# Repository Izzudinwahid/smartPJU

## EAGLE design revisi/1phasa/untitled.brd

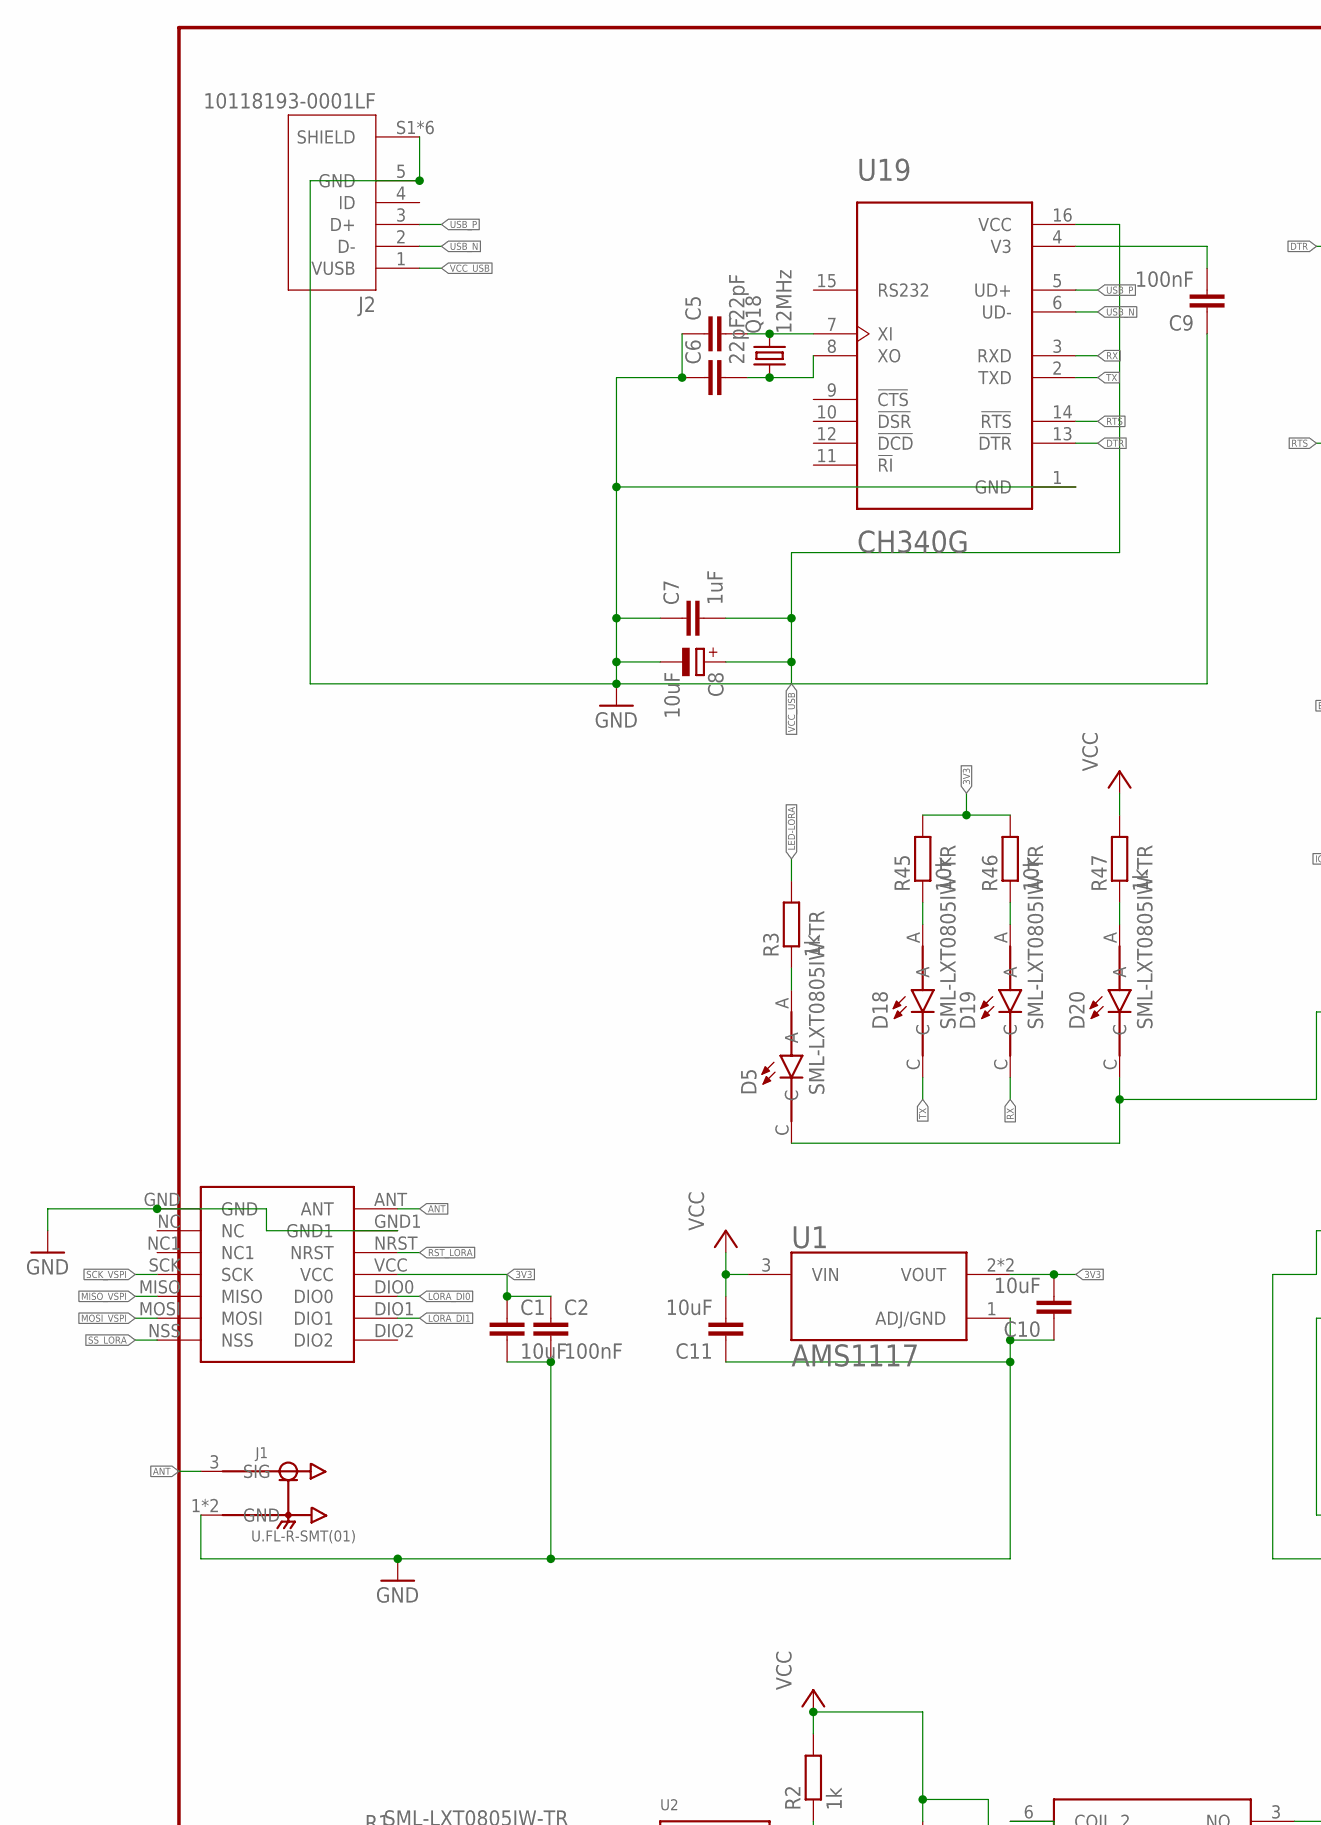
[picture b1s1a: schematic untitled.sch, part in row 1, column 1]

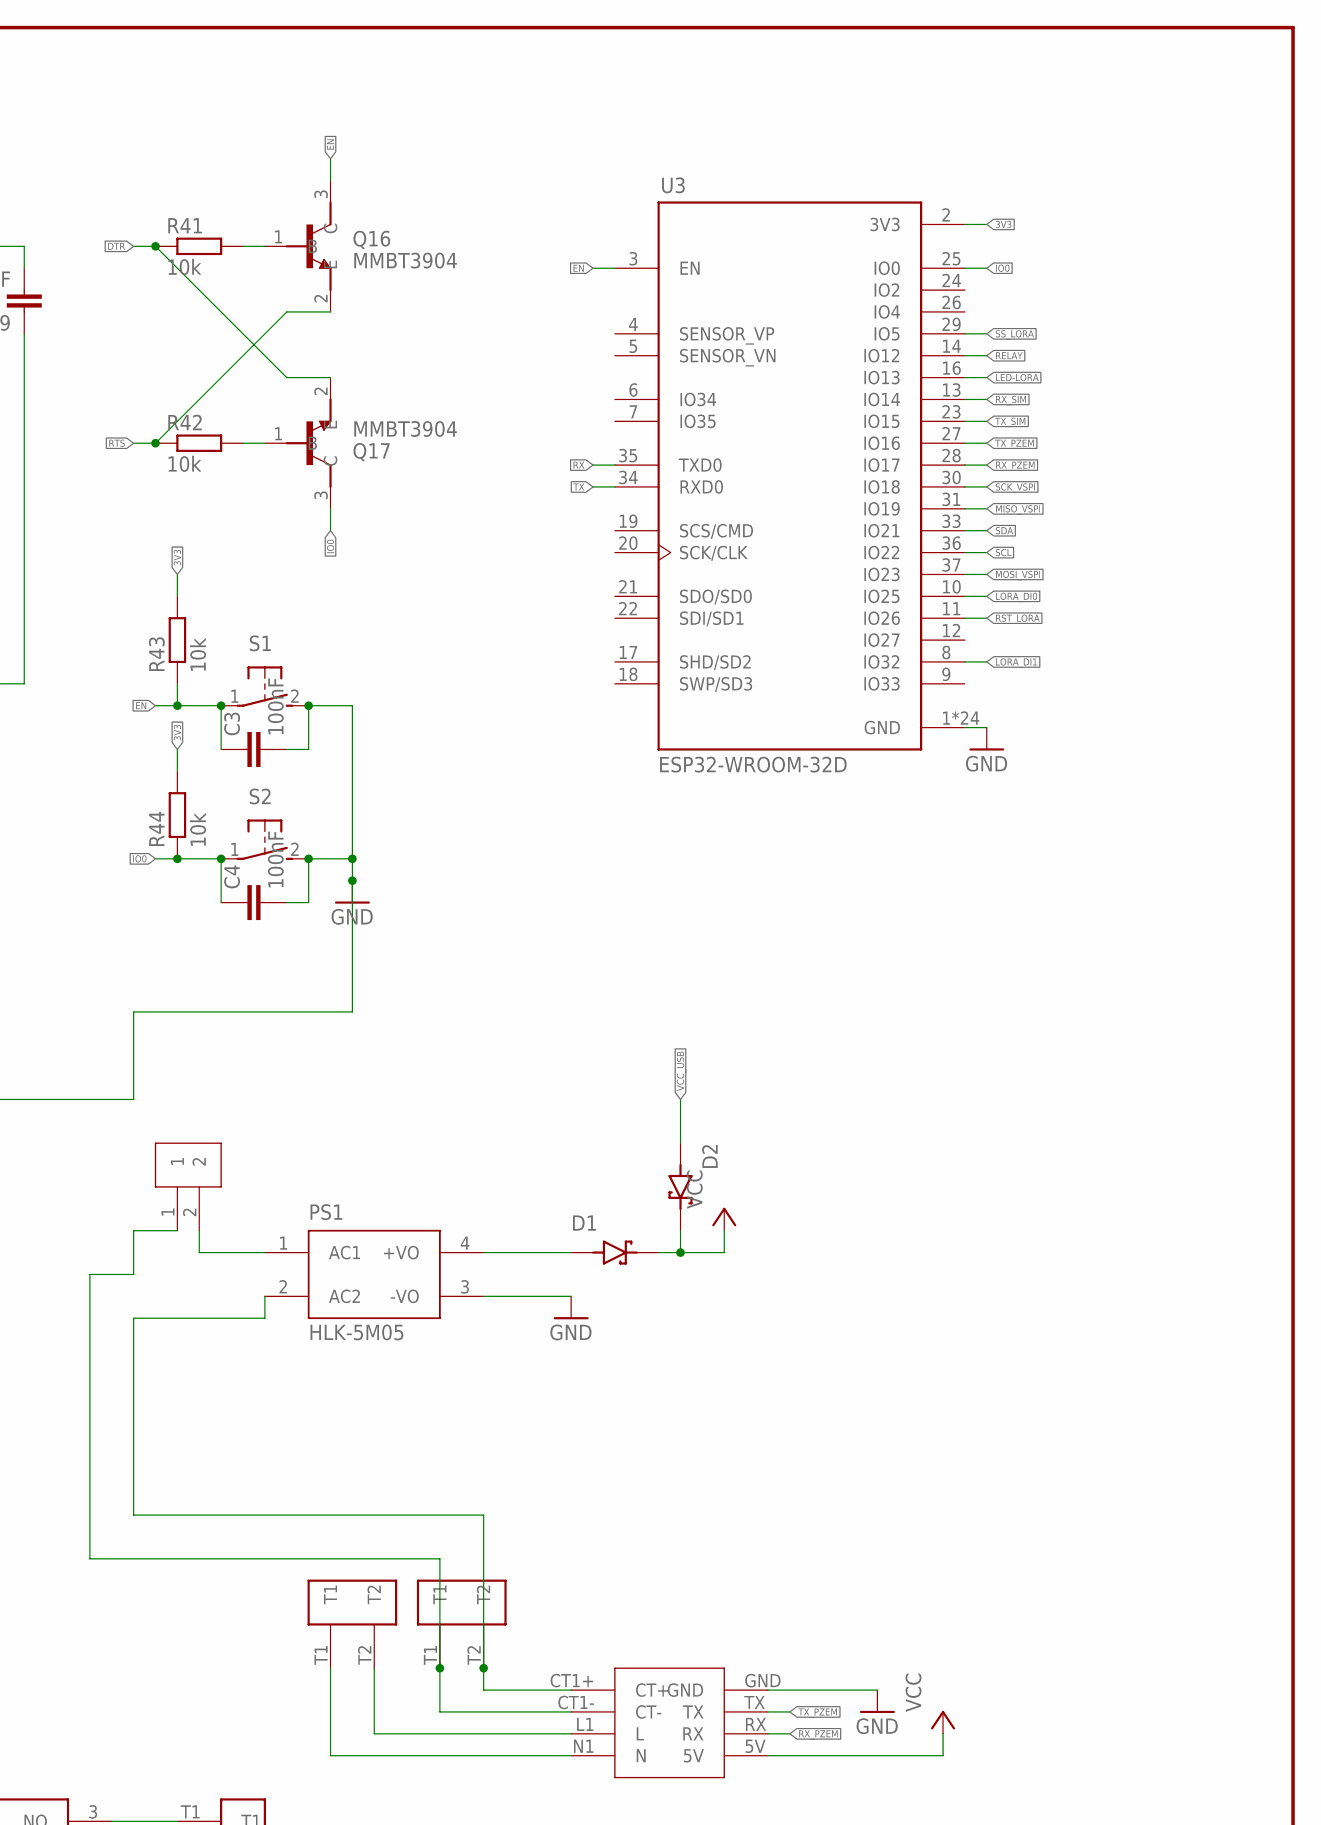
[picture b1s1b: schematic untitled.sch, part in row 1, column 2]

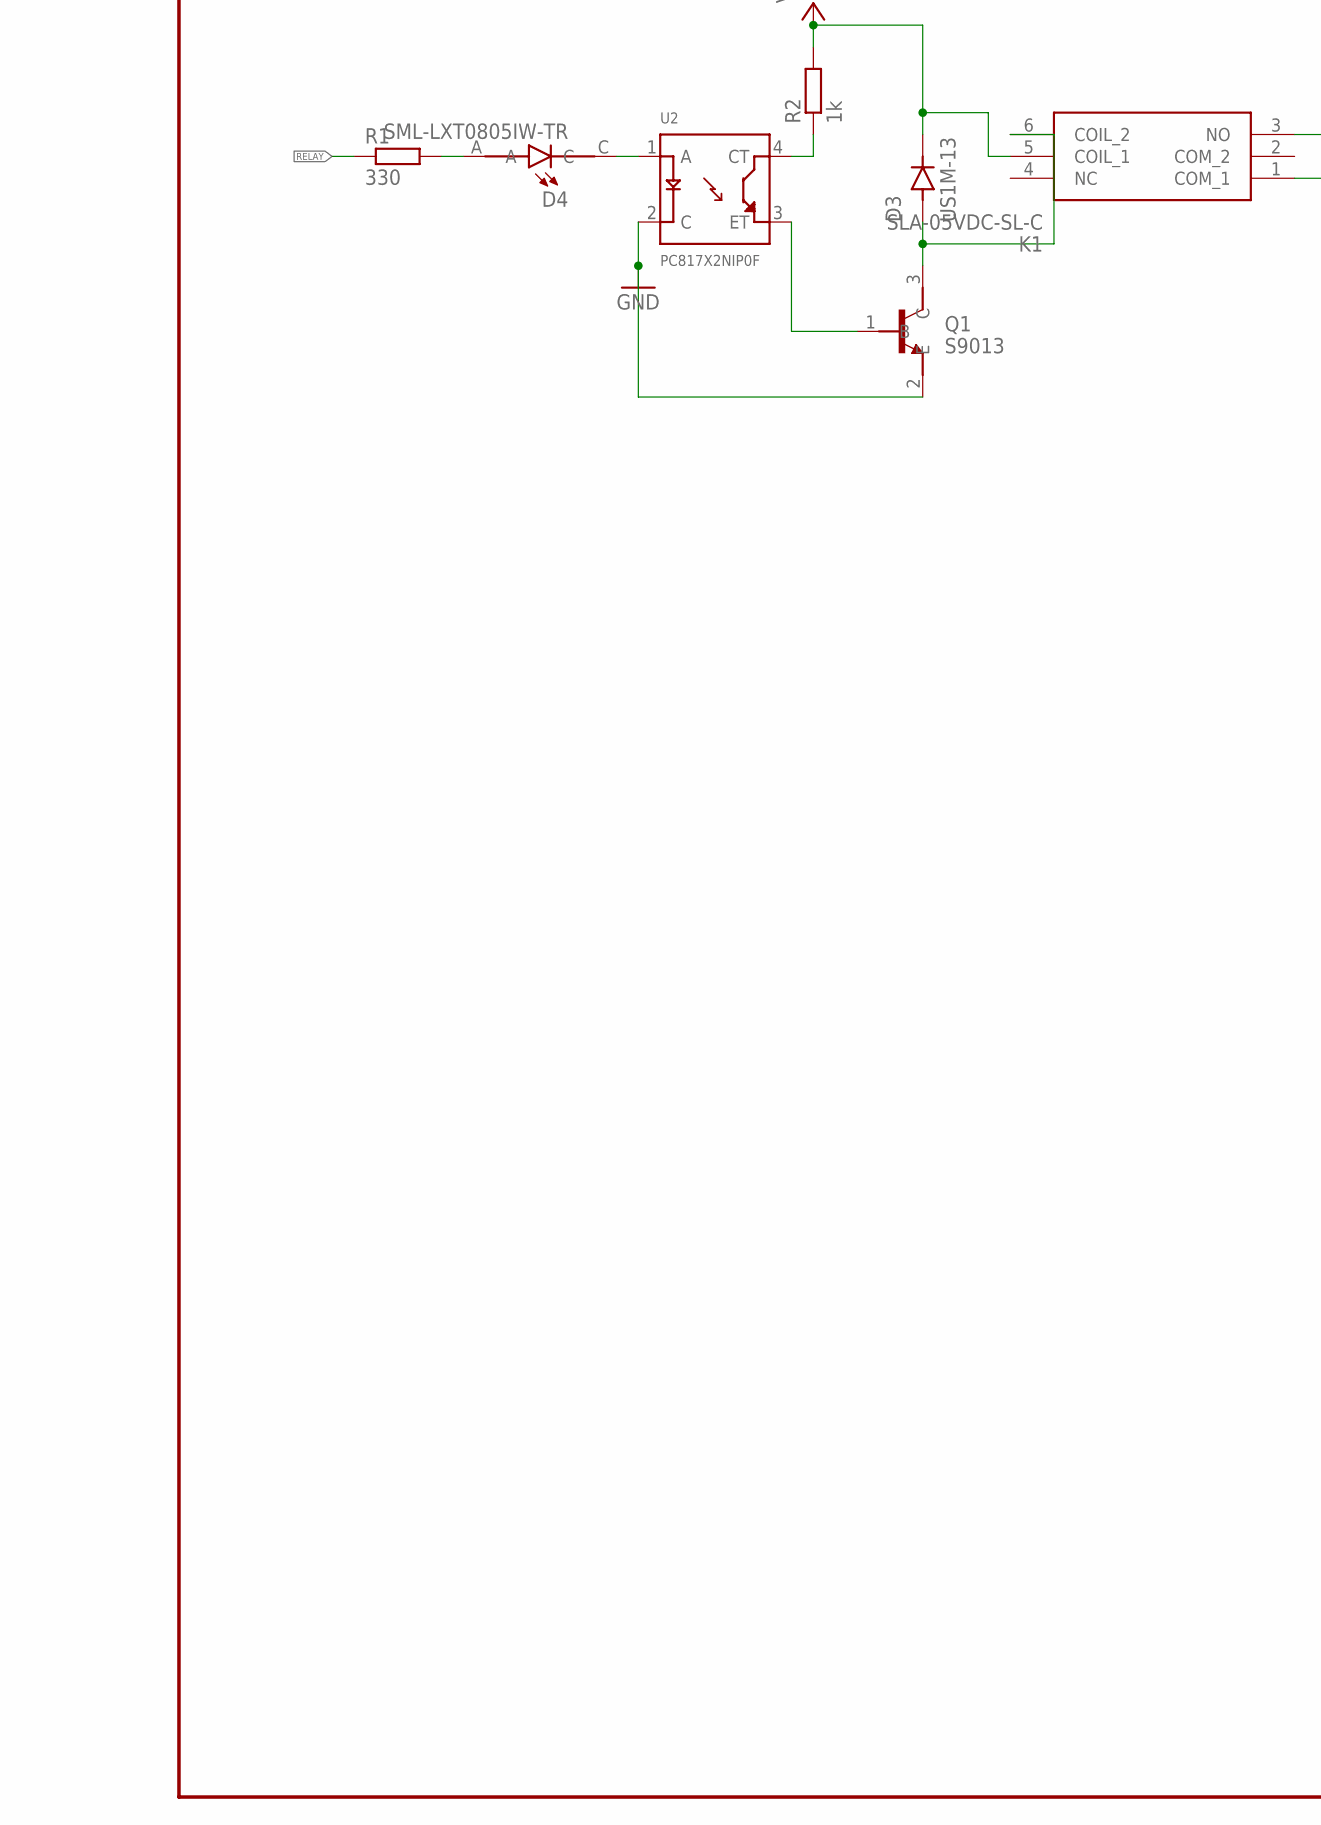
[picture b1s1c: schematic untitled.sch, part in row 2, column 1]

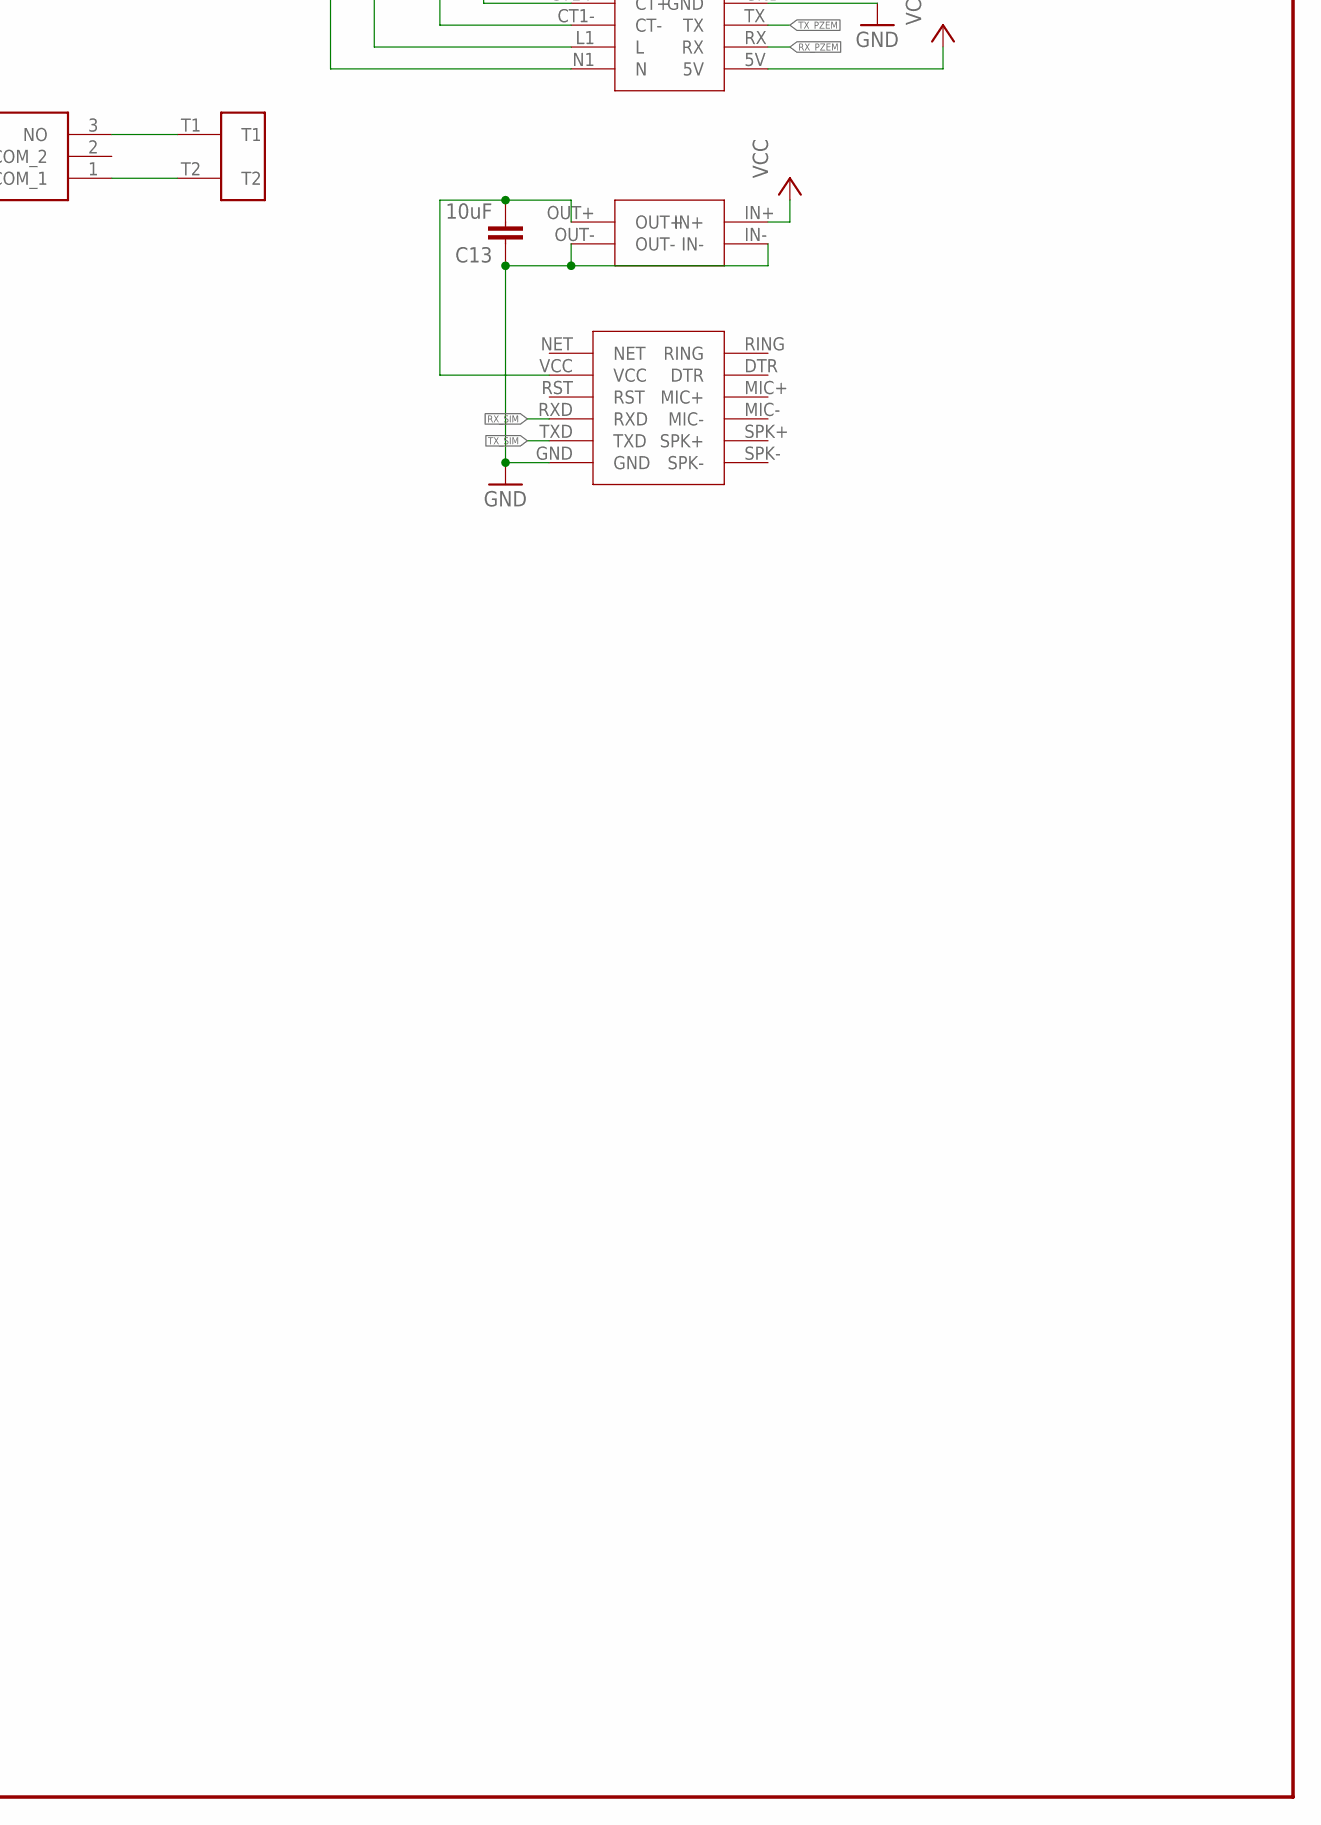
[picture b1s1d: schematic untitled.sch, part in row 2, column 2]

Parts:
C1, C10, C11, C13: 10uF; C0805K
C2, C3, C4, C9: 100nF; C0805K
C5, C6: 22pF; C0805K
C7: 1uF; C0805K
C8: 10uF; 153CLV-0505
D1, D2: 1N5819HW-7; SOD3715X145N
D3: US1M-13; DIOM5226X240N
D4, D5, D18, D19, D20: SML-LXT0805IW-TR; LEDC2012X120N
FUSE-KOTAK1: FUSE-KOTAK
J1: U.FL-R-SMT(01); HRS_U.FL-R-SMT(01)
J2: 10118193-0001LF; FCI_10118193-0001LF
K1: SLA-05VDC-SL-C; SLA05VDCSLC
LORA-NICERF-V1: LORA-NICERF-V2
MINI1: MINI360
PS1: HLK-5M05; CONV_HLK-5M05
PZEM004T1: PZEM004T
Q1: S9013; SOT95P240X120-3N
Q16, Q17: MMBT3904; SOT95P240X120-3N
Q18: 12MHz; SM49
R1: 330; R0805
R2, R3, R47: 1k; R0805
R41, R42, R43, R44, R45, R46: 10k; R0805
S1, S2: 31-XX; B3F-31XX
SIM800L1: SIM800L
TB7.2, TB7.3, TB7.4: TB7.62
U1: AMS1117; SOT229P700X180-4N
U2: PC817X2NIP0F; SOT254P975X400-4N
U3: ESP32-WROOM-32D; MODULE_ESP32-WROOM-32D
U19: CH340G; SOIC127P600X180-16N

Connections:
3V3: C1.1, C2.1, C10.2, LORA-NICERF-V1.VCC, R43.2, R44.2, R45.2, R46.2, U1.2 (VOUT), U1.4 (VOUT), U3.2 (3V3)
ANT: J1.3 (SIG), LORA-NICERF-V1.ANT
DTR: Q17.2 (E), R41.1, U19.13 (!DTR)
EN: C3.1, Q16.3 (C), R43.1, S1.1, U3.3 (EN)
GND: C1.2, C2.2, C3.2, C4.2, C5.1, C6.1, C7.1, C8.-, C9.1, C10.1, C11.1, C13.1, D5.C, D20.C, J1.1 (GND), J1.2 (GND), J2.5 (GND), J2.S1 (SHIELD), J2.S2 (SHIELD), J2.S3 (SHIELD), J2.S4 (SHIELD), J2.S5 (SHIELD), J2.S6 (SHIELD), LORA-NICERF-V1.GND, LORA-NICERF-V1.GND1, MINI1.IN-, MINI1.OUT-, PS1.3 (-VO), PZEM004T1.GND, Q1.2 (E), S1.2 (S), S2.2 (S), SIM800L1.GND, U1.1 (ADJ/GND), U2.2 (C), U3.1 (GND), U3.15 (GND), U3.38 (GND), U3.39_1 (GND), U3.39_2 (GND), U3.39_3 (GND), U3.39_4 (GND), U3.39_5 (GND), U3.39_6 (GND), U3.39_7 (GND), U3.39_8 (GND), U3.39_9 (GND), U3.39_10 (GND), U3.39_11 (GND), U3.39_12 (GND), U3.39_13 (GND), U3.39_14 (GND), U3.39_15 (GND), U3.39_16 (GND), U3.39_17 (GND), U3.39_18 (GND), U3.39_19 (GND), U3.39_20 (GND), U3.39_21 (GND), U19.1 (GND)
IO0: C4.1, Q17.3 (C), R44.1, S2.1, U3.25 (IO0)
LED-LORA: R3.2, U3.16 (IO13)
LORA_DI0: LORA-NICERF-V1.DIO0, U3.10 (IO25)
LORA_DI1: LORA-NICERF-V1.DIO1, U3.8 (IO32)
MISO_VSPI: LORA-NICERF-V1.MISO, U3.31 (IO19)
MOSI_VSPI: LORA-NICERF-V1.MOSI, U3.37 (IO23)
unnamed: FUSE-KOTAK1.2, PS1.1 (AC1)
unnamed: PS1.2 (AC2), PZEM004T1.CT1+ (CT+), TB7.3.T2
unnamed: D1.A, PS1.4 (+VO)
unnamed: D4.C, U2.1 (A)
unnamed: R2.1, U2.4 (CT)
unnamed: Q1.1 (B), U2.3 (ET)
unnamed: D3.A, K1.6 (COIL_2), Q1.3 (C)
unnamed: D4.A, R1.2
unnamed: K1.1 (COM_1), TB7.2.T2
unnamed: Q17.1 (B), R42.2
unnamed: D5.A, R3.1
unnamed: C13.2, MINI1.OUT+, SIM800L1.VCC
unnamed: FUSE-KOTAK1.1, PZEM004T1.CT1- (CT-), TB7.3.T1
unnamed: PZEM004T1.L1 (L), TB7.4.T2
unnamed: PZEM004T1.N1 (N), TB7.4.T1
unnamed: K1.3 (NO), TB7.2.T1
unnamed: Q16.1 (B), R41.2
unnamed: C5.2, Q18.2, U19.7 (XI)
unnamed: C6.2, Q18.1, U19.8 (XO)
unnamed: C9.2, U19.4 (V3)
unnamed: D18.A, R45.1
unnamed: D19.A, R46.1
unnamed: D20.A, R47.1
RELAY: R1.1, U3.14 (IO12)
RST_LORA: LORA-NICERF-V1.NRST, U3.11 (IO26)
RTS: Q16.2 (E), R42.1, U19.14 (!RTS)
RX: D19.C, U3.35 (TXD0), U19.3 (RXD)
RX_PZEM: PZEM004T1.RX, U3.28 (IO17)
RX_SIM: SIM800L1.RXD, U3.13 (IO14)
SCK_VSPI: LORA-NICERF-V1.SCK, U3.30 (IO18)
SCL: U3.36 (IO22)
SDA: U3.33 (IO21)
SS_LORA: LORA-NICERF-V1.NSS, U3.29 (IO5)
TX: D18.C, U3.34 (RXD0), U19.2 (TXD)
TX_PZEM: PZEM004T1.TX, U3.27 (IO16)
TX_SIM: SIM800L1.TXD, U3.23 (IO15)
USB_N: J2.2 (D-), U19.6 (UD-)
USB_P: J2.3 (D+), U19.5 (UD+)
VCC: C11.2, D1.C (K), D2.C (K), D3.C (K), K1.5 (COIL_1), MINI1.IN+, PZEM004T1.5V, R2.2, R47.2, U1.3 (VIN)
VCC_USB: C7.2, C8.+, D2.A, J2.1 (VUSB), U19.16 (VCC)

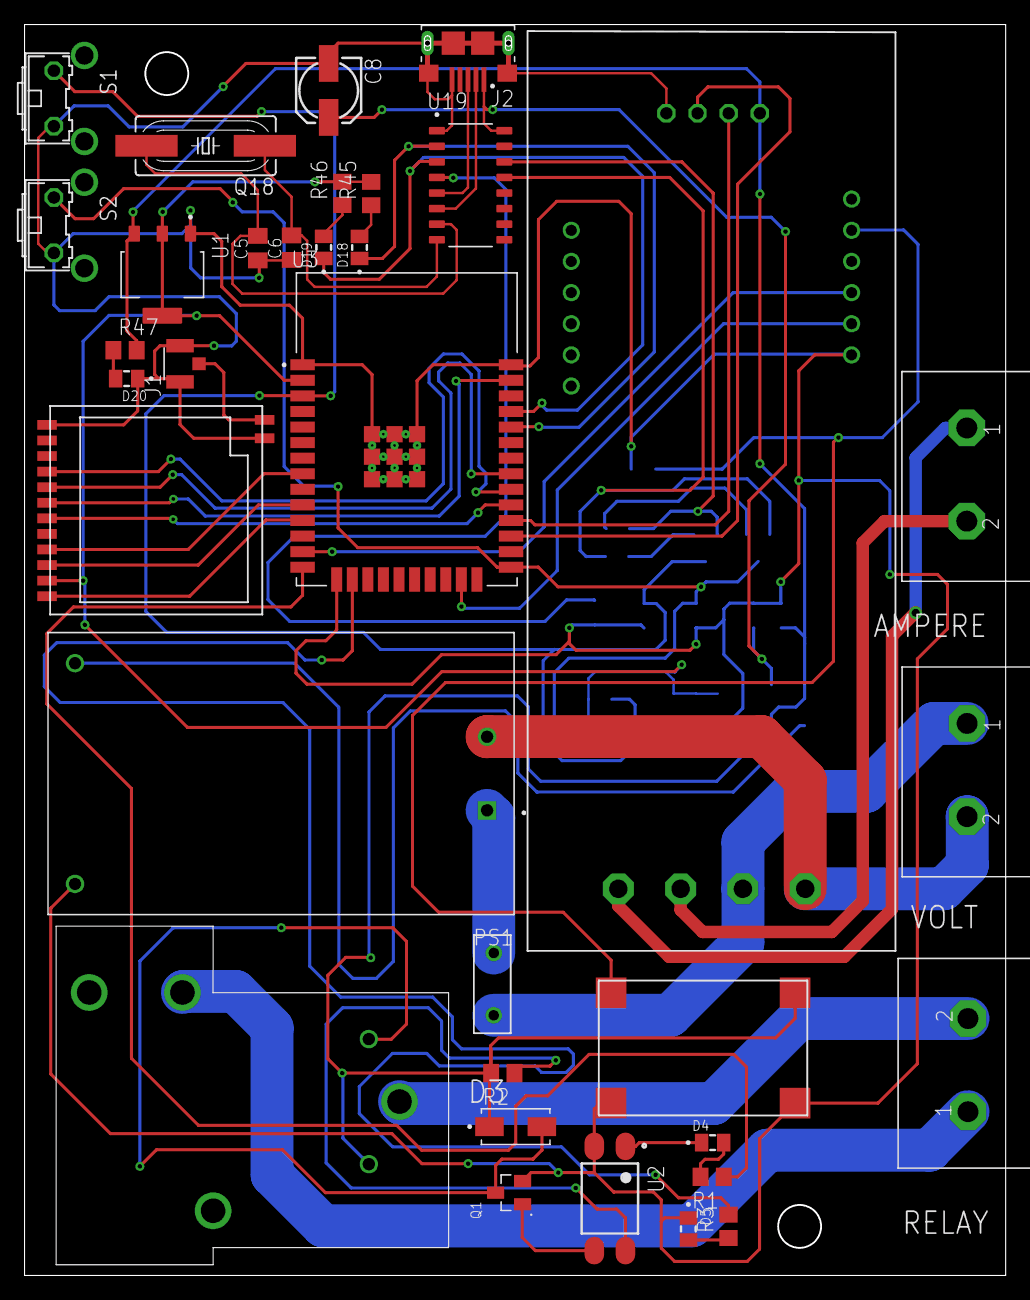
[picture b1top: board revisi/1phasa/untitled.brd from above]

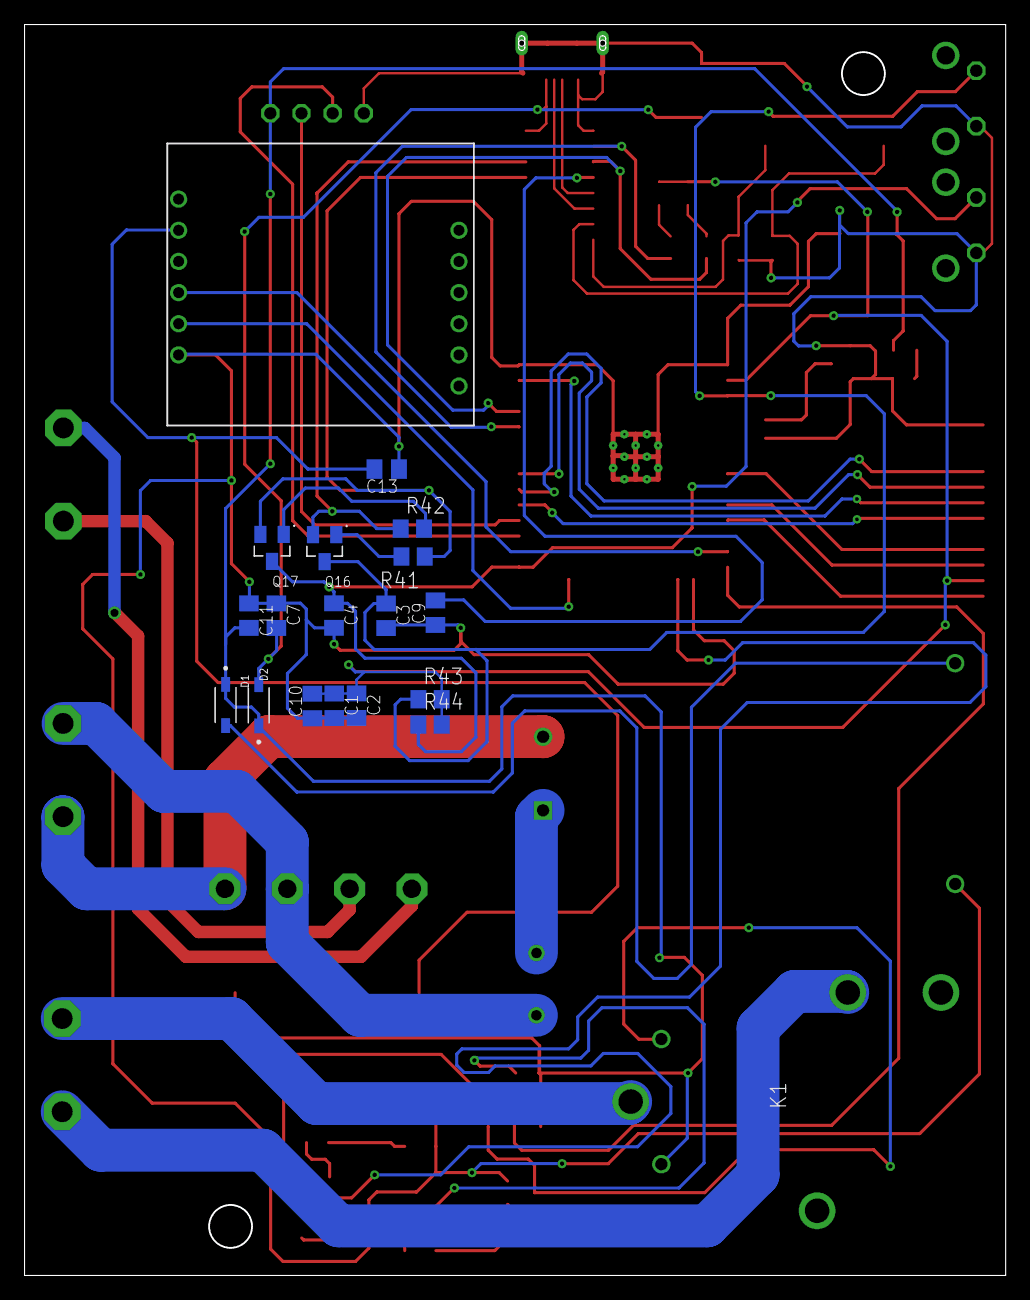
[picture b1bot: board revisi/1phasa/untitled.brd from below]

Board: 2 copper layers, 80.0 x 102.0 mm, 52 parts (19 on the bottom side), 49 nets.

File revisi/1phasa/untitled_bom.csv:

Comment,Designator,Footprint,LCSC Part #
,S1,B3F-31XX,
,S2,B3F-31XX,
,FUSE-KOTAK1,FUSE-KOTAK,
,LORA-NICERF-V1,LORA-NICERF-V2,
,MINI1,MINI360,
,PZEM004T1,PZEM004T,
,SIM800L1,SIM800L,
,TB7.2,TB7.62,
,TB7.3,TB7.62,
,TB7.4,TB7.62,
1N5819HW-7,D1 D2,SOD3715X145N,
1uF,C7,C0805K,
10k,R2 R3 R41 R42 R43 R44 R45 R46 R47,R0805,
10uF,C8,153CLV-0505,
10uF,C1 C10 C11 C13,C0805K,
12MHz,Q18,SM49,
22pF,C5 C6,C0805K,
100nF,C2 C3 C4 C9,C0805K,
330,R1,R0805,
10118193-0001LF,J2,FCI_10118193-0001LF,
AMS1117,U1,SOT229P700X180-4N,
CH340G,U19,SOIC127P600X180-16N,
ESP32-WROOM-32D,U3,MODULE_ESP32-WROOM-32D,
HLK-5M05,PS1,CONV_HLK-5M05,
MMBT3904,Q16 Q17,SOT95P240X120-3N,
PC817X2NIP0F,U2,SOT254P975X400-4N,
S9013,Q1,SOT95P240X120-3N,
SLA-05VDC-SL-C,K1,SLA05VDCSLC,
SML-LXT0805IW-TR,D4 D5 D18 D19 D20,LEDC2012X120N,
U.FL-R-SMT(01),J1,HRS_U.FL-R-SMT(01),
US1M-13,D3,DIOM5226X240N,

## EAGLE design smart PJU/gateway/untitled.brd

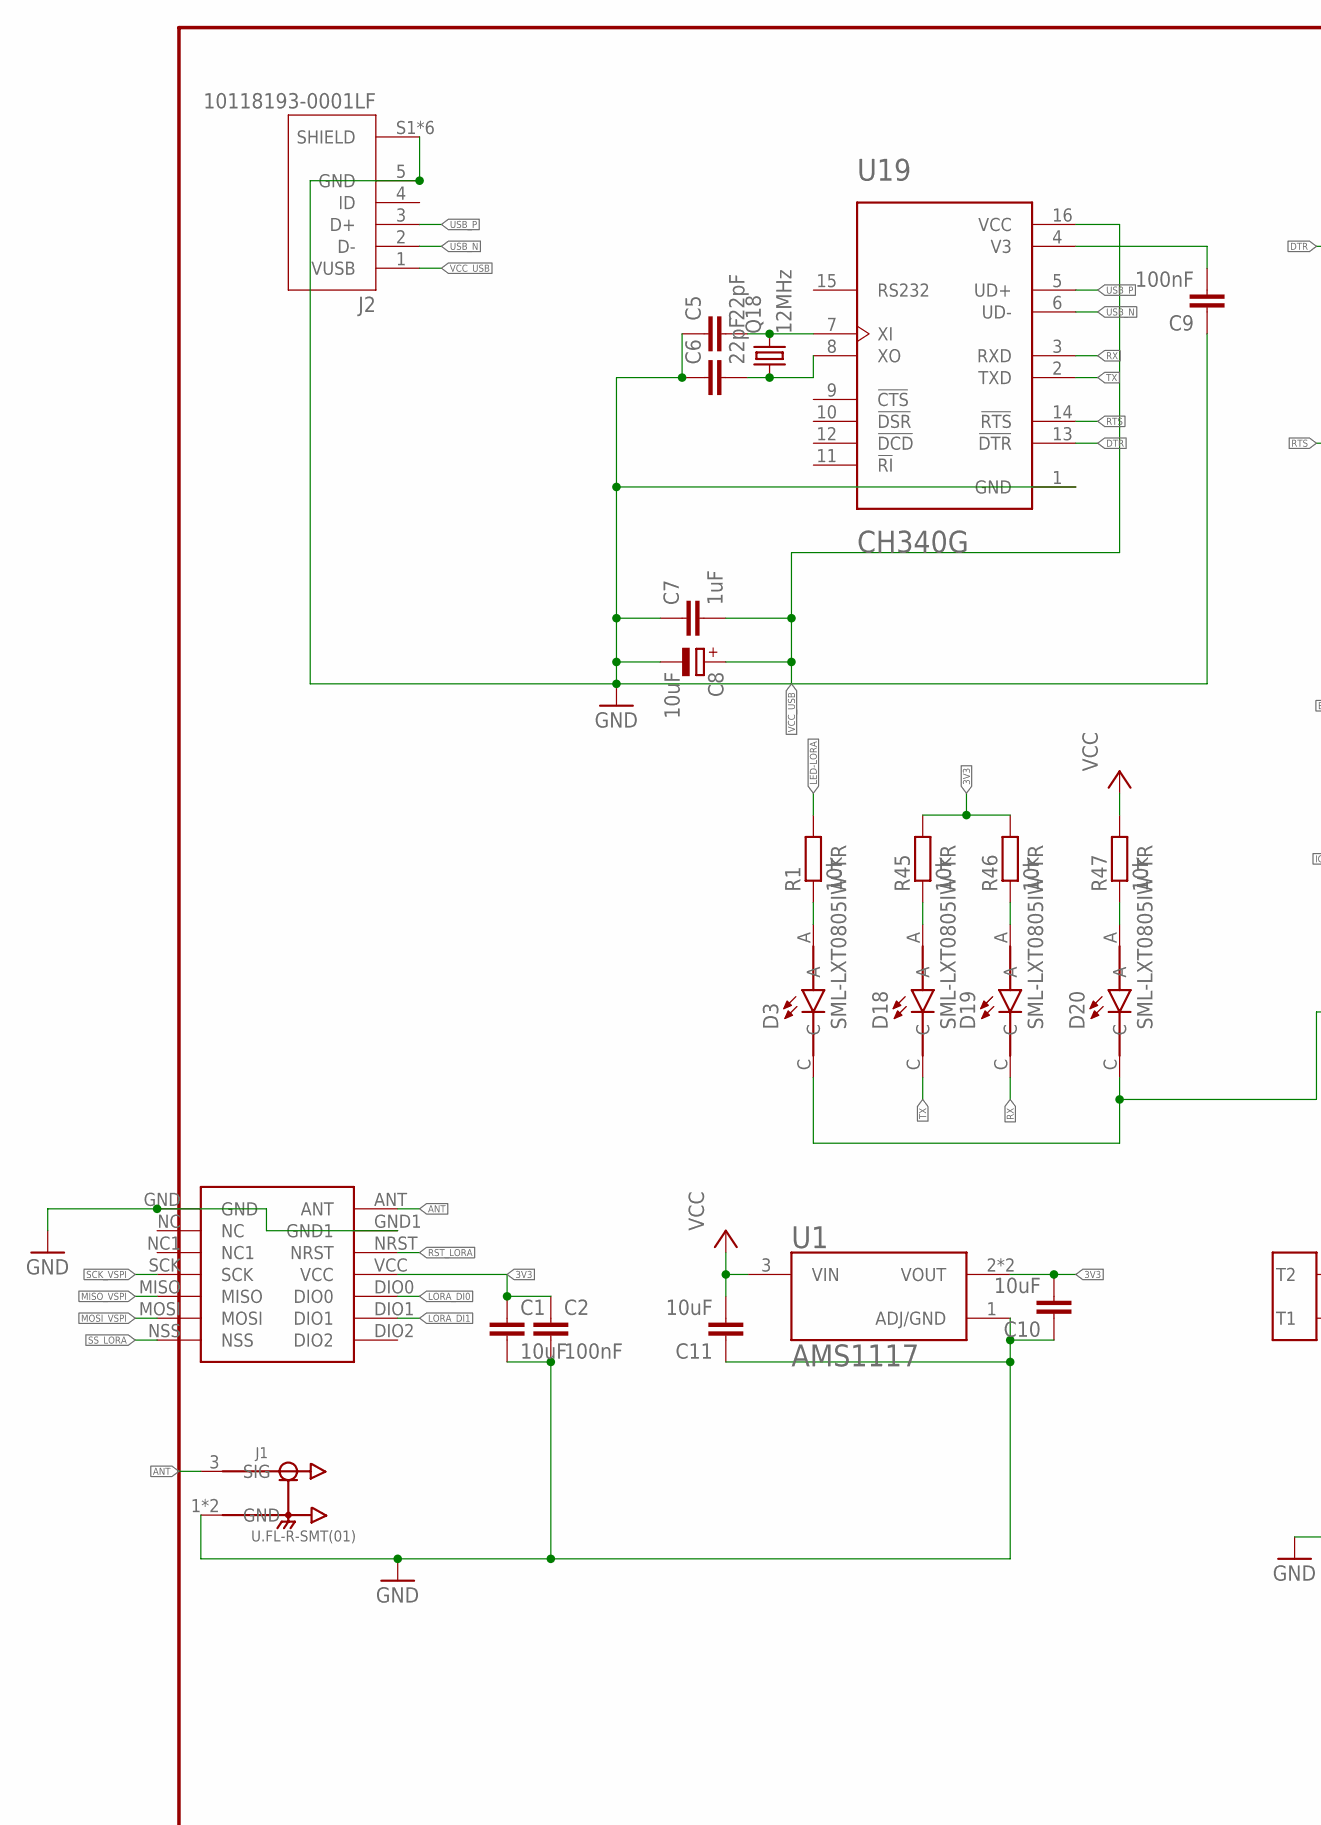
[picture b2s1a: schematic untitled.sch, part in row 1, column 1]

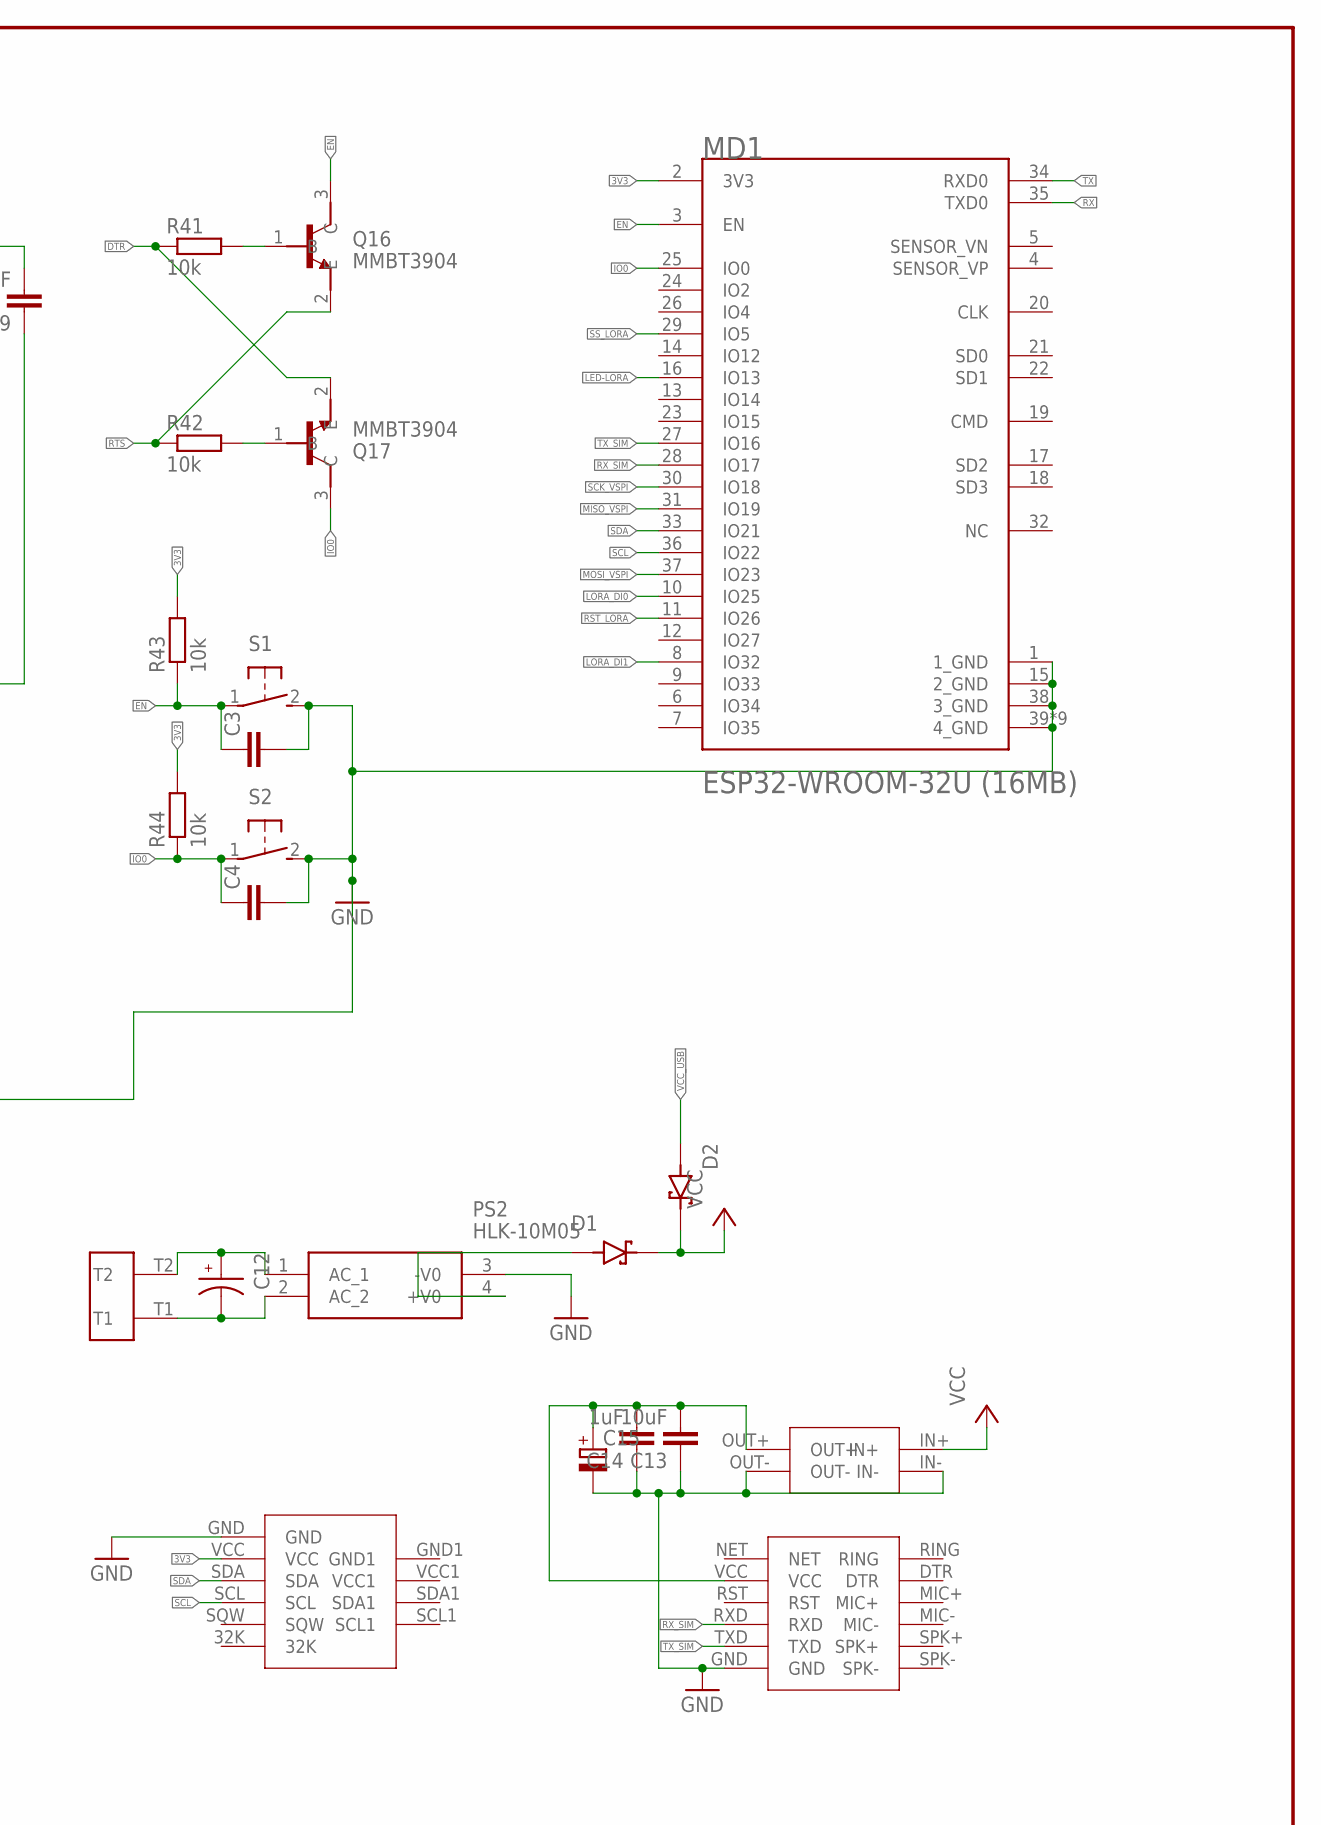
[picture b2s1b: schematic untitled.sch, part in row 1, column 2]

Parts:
C1, C10, C11, C13: 10uF; C0805K
C2, C9: 100nF; C0805K
C3, C4: C-EUC0805K; C0805K
C5, C6: 22pF; C0805K
C7, C14: 1uF; C0805K
C8: 10uF; 153CLV-0505
C12: UPM2E100MHD1TO; CAPPRD500W60D1250H2200
C15: CPOL-EU153CLV-0505; 153CLV-0505
D1, D2: 1N5819HW-7; SOD3715X145N
D3, D18, D19, D20: SML-LXT0805IW-TR; LEDC2012X120N
J1: U.FL-R-SMT(01); HRS_U.FL-R-SMT(01)
J2: 10118193-0001LF; FCI_10118193-0001LF
LORA-NICERF-V1: LORA-NICERF-V2
MD1: ESPRESSIF_SYSTEMS_ESP32-WROOM-32U_16MBESPRESSIF_S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; ESPRESSIF_SYSTEMS_ESP32-WROOM-32U_16MB_0
MINI1: MINI360
PS2: HLK-10M05; HLK10M05
Q16, Q17: MMBT3904; SOT95P240X120-3N
Q18: 12MHz; SM49
R1, R41, R42, R43, R44, R45, R46, R47: 10k; R0805
RTC1: RTC3231
S1, S2: 31-XX; B3F-31XX
SIM800L1: SIM800L
TB7.1: TB7.62
U1: AMS1117; SOT229P700X180-4N
U19: CH340G; SOIC127P600X180-16N

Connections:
3V3: C1.1, C2.1, C10.2, LORA-NICERF-V1.VCC, MD1.2 (3V3), R43.2, R44.2, R45.2, R46.2, RTC1.VCC, U1.2 (VOUT), U1.4 (VOUT)
ANT: J1.3 (SIG), LORA-NICERF-V1.ANT
DTR: Q17.2 (E), R41.1, U19.13 (!DTR)
EN: C3.1, MD1.3 (EN), Q16.3 (C), R43.1, S1.1
GND: C1.2, C2.2, C3.2, C4.2, C5.1, C6.1, C7.1, C8.-, C9.1, C10.1, C11.1, C13.1, C14.1, C15.-, D3.C, D20.C, J1.1 (GND), J1.2 (GND), J2.5 (GND), J2.S1 (SHIELD), J2.S2 (SHIELD), J2.S3 (SHIELD), J2.S4 (SHIELD), J2.S5 (SHIELD), J2.S6 (SHIELD), LORA-NICERF-V1.GND, LORA-NICERF-V1.GND1, MD1.1 (1_GND), MD1.15 (2_GND), MD1.38 (3_GND), MD1.39 (4_GND), MD1.39-2 (4_GND), MD1.39-3 (4_GND), MD1.39-4 (4_GND), MD1.39-5 (4_GND), MD1.39-6 (4_GND), MD1.39-7 (4_GND), MD1.39-8 (4_GND), MD1.39-9 (4_GND), MINI1.IN-, MINI1.OUT-, PS2.3 (-V0), RTC1.GND, S1.2 (S), S2.2 (S), SIM800L1.GND, U1.1 (ADJ/GND), U19.1 (GND)
IO0: C4.1, MD1.25 (IO0), Q17.3 (C), R44.1, S2.1
LED-LORA: MD1.16 (IO13), R1.2
LORA_DI0: LORA-NICERF-V1.DIO0, MD1.10 (IO25)
LORA_DI1: LORA-NICERF-V1.DIO1, MD1.8 (IO32)
MISO_VSPI: LORA-NICERF-V1.MISO, MD1.31 (IO19)
MOSI_VSPI: LORA-NICERF-V1.MOSI, MD1.37 (IO23)
unnamed: C12.P, PS2.1 (AC_1), TB7.1.T2
unnamed: C12.N, PS2.2 (AC_2), TB7.1.T1
unnamed: D1.A, PS2.4 (+V0)
unnamed: C13.2, C14.2, C15.+, MINI1.OUT+, SIM800L1.VCC
unnamed: D3.A, R1.1
unnamed: Q17.1 (B), R42.2
unnamed: Q16.1 (B), R41.2
unnamed: C5.2, Q18.2, U19.7 (XI)
unnamed: C6.2, Q18.1, U19.8 (XO)
unnamed: C9.2, U19.4 (V3)
unnamed: D18.A, R45.1
unnamed: D19.A, R46.1
unnamed: D20.A, R47.1
RST_LORA: LORA-NICERF-V1.NRST, MD1.11 (IO26)
RTS: Q16.2 (E), R42.1, U19.14 (!RTS)
RX: D19.C, MD1.35 (TXD0), U19.3 (RXD)
RX_SIM: MD1.28 (IO17), SIM800L1.RXD
SCK_VSPI: LORA-NICERF-V1.SCK, MD1.30 (IO18)
SCL: MD1.36 (IO22), RTC1.SCL
SDA: MD1.33 (IO21), RTC1.SDA
SS_LORA: LORA-NICERF-V1.NSS, MD1.29 (IO5)
TX: D18.C, MD1.34 (RXD0), U19.2 (TXD)
TX_SIM: MD1.27 (IO16), SIM800L1.TXD
USB_N: J2.2 (D-), U19.6 (UD-)
USB_P: J2.3 (D+), U19.5 (UD+)
VCC: C11.2, D1.C (K), D2.C (K), MINI1.IN+, R47.2, U1.3 (VIN)
VCC_USB: C7.2, C8.+, D2.A, J2.1 (VUSB), U19.16 (VCC)
